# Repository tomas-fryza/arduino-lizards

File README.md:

# Measuring track for lizards

* [TODO](#TODO)
* [About](#About)
* [Usage](#Usage)
  * [PuTTY for Windows and Linux](#PuTTY-for-Windows-and-Linux)
  * [Terminal for Windows](#Terminal-for-Windows)
  * [Termite for Windows](#Termite-for-Windows)
* [Programming Arduino using PlatformIO](#Programming-Arduino-using-PlatformIO)
* [References](#References)

## TODO

* [x] Instructions for use & program
* [x] Logging data to a file
* [x] Selecting a suitable Monitor program (PuTTY, Terminal, Terminte, PlatformIO, ...)
* [x] Strengthen the mechanics
* [x] Add "start box"
* [x] Add (semi)waterproof paint
* [x] Cover electronics, 3D printing
* [x] Q: Consumption? A: approx. 350 milliamps
* [x] Q: IR wavelength A: 940 nm
* [ ] Q: Do I need to install USB driver? A: ??

## About

The measuring path contains 11 optical wounds, i.e. pairs of 940 nm infrared diodes and phototransistors. The first gate is the starting gate, the others are spaced 10 centimeters apart. The length of the track is thus 1 meter. Combine temperature and humidity sensor is used as well.

The ATmega328P microcontroller on the Arduino Nano board provides data acquisition from optical gates, time, temperature and humidity measurement, and data sending. The measuring track is powered via a mini USB connector, and at the same time, all data about the measurement progress is sent to the computer/laptop via this USB. Values are separated by semicolumn ";" symbol and can be subsequently processed, for example, in Excel.

## Usage

Once the microcontroller is programmed, on the PC/laptop just run one of the programs that can communicate with the serial port, such as PuTTY, Terminal, Termite, or other.

Perform the following steps to measure the speed of lizards:

1. Connect your computer/laptop to the Arduino board using a USB cable.

2. Run PuTTY, Terminal, Termite, or other serial terminal.

3. Configure terminal to save measured data to log text file.

4. Press `S` on keyboard to start the measurement. Status LED on Arduino board is turn on.

5. Place the lizard in the starting position and let it run through the entire track.

6. The individual times are written to the serial terminal (and the log file) after all gates have been interrupted or after the maximum time has expired. This is set to 60 seconds and can be reprogrammed in the Arduino Nano.

7. Go back to point 4 and repeat.

### PuTTY for Windows and Linux

1. Download, install, and run PuTTY open-source application for [Windows](https://putty.org/) or [Linux](https://www.tecmint.com/install-putty-on-linux/).

2. Set the following parameters:

   a. Category: Session Logging: **Printable output**

   b. Select Log file name, such as: `C:\Documents\your-user-name\putty_&Y&M&D-&T.log`

   c. Change Category to **Session** and select Connection type: **Serial**

   d. Serial line: put your com port, such as **COM5** (Windows) or `/dev/ttyUSB0` (Linux)

      > **Help:** To get the port name, run the Device Manager on Windows or type `dmesg` command to Terminal in Linux.

   e. Speed: **9600**

   f. Name Save Sessions: **LIZARDS** and click on **Save** button

   g. Anytime in the future, there is no need to configure PuTTY again, just double click on saved default settings **LIZARDS** to open the connection.

   h. Press `S` on keyboard to start each measurement.

   i. Values are saved to your log file.

### Terminal for Windows

1. Download, unzip, and run the [Terminal](https://sites.google.com/site/terminalbpp/) application.

2. TBD

### Termite for Windows

1. Download, install, and run [Termite](https://www.compuphase.com/software_termite.htm#EDITHISTORY) application.

2. TBD

## Programming Arduino using PlatformIO

1. Follow [Installation](https://github.com/tomas-fryza/digital-electronics-2/wiki/How-to-use-AVR-template-with-PlatformIO) instruction and download & install Visual Studio Code and PlatformIO plugin.

2. Download this repository, ie. in [browser](https://github.com/tomas-fryza/arduino-lizards), click on green `<> Code` button and select `Download ZIP`. Extract zip file to your local computer.

3. In Visual Studio Code, select **File > Open Folder...** and browse to `arduino-lizards/software/lizards` extracted folder.

4. In `platformio.ini` configuration file change your port name, such as COM5 for Windows:

   ```asm
   ; Custom monitor port
   ; Windows:
   monitor_port = COM[5]
   ; Linux:
   ; monitor_port = /dev/ttyUSB0
   ```

5. The application is programmed in C++ and is located in the file `src > main.cpp`

6. Compile the code, run the application, and open Serial Monitor to control it.

## References

1. Michaela Ryšavá. [Vývoj systému pro měření pohybových schopností malých živočichů](https://www.vut.cz/studenti/zav-prace/detail/141521)

2. Les Pounder. [How To Detect the COM Port for Any Serial Device in Windows](https://www.tomshardware.com/how-to/detect-com-port-windows-serial-port-notifier)

3. Martins D. Okoi. [How to Install PuTTY on Linux](https://www.tecmint.com/install-putty-on-linux/)

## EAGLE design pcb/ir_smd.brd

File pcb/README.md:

# List of components

Symbol | Value | Package | Description
 :--   | :--   | :--     | :--
R1 | 10k | SMD 0805 | Resistor
R2 | 50 | SMD 0805 | Resistor
C | 100n | SMD 0603 | Capacitor
LM393D | | S08 | Dual differential comparator
L-53F3BT | | THT | LED IR, 940nm, 5mm
503PTC2E | | THT | Phototransistor, IR Detector 940nm
DG350-3.50-05P-14-02A | | | Screw terminal
BL 1 34 G | | | Female headers

## Possible future revisions

* switching transistors for IR leds
* smd packages for both IR leds and phototransistors
* more accurate temperature measurement
* lower consumption, battery powered
* ESP32, wi-fi/bluetooth comm?
* onboard logging: eeprom, sd card, ...
* display, button
* multiple IR LEDs on top of each other; the possibility of setting the necessary height of the optical gate

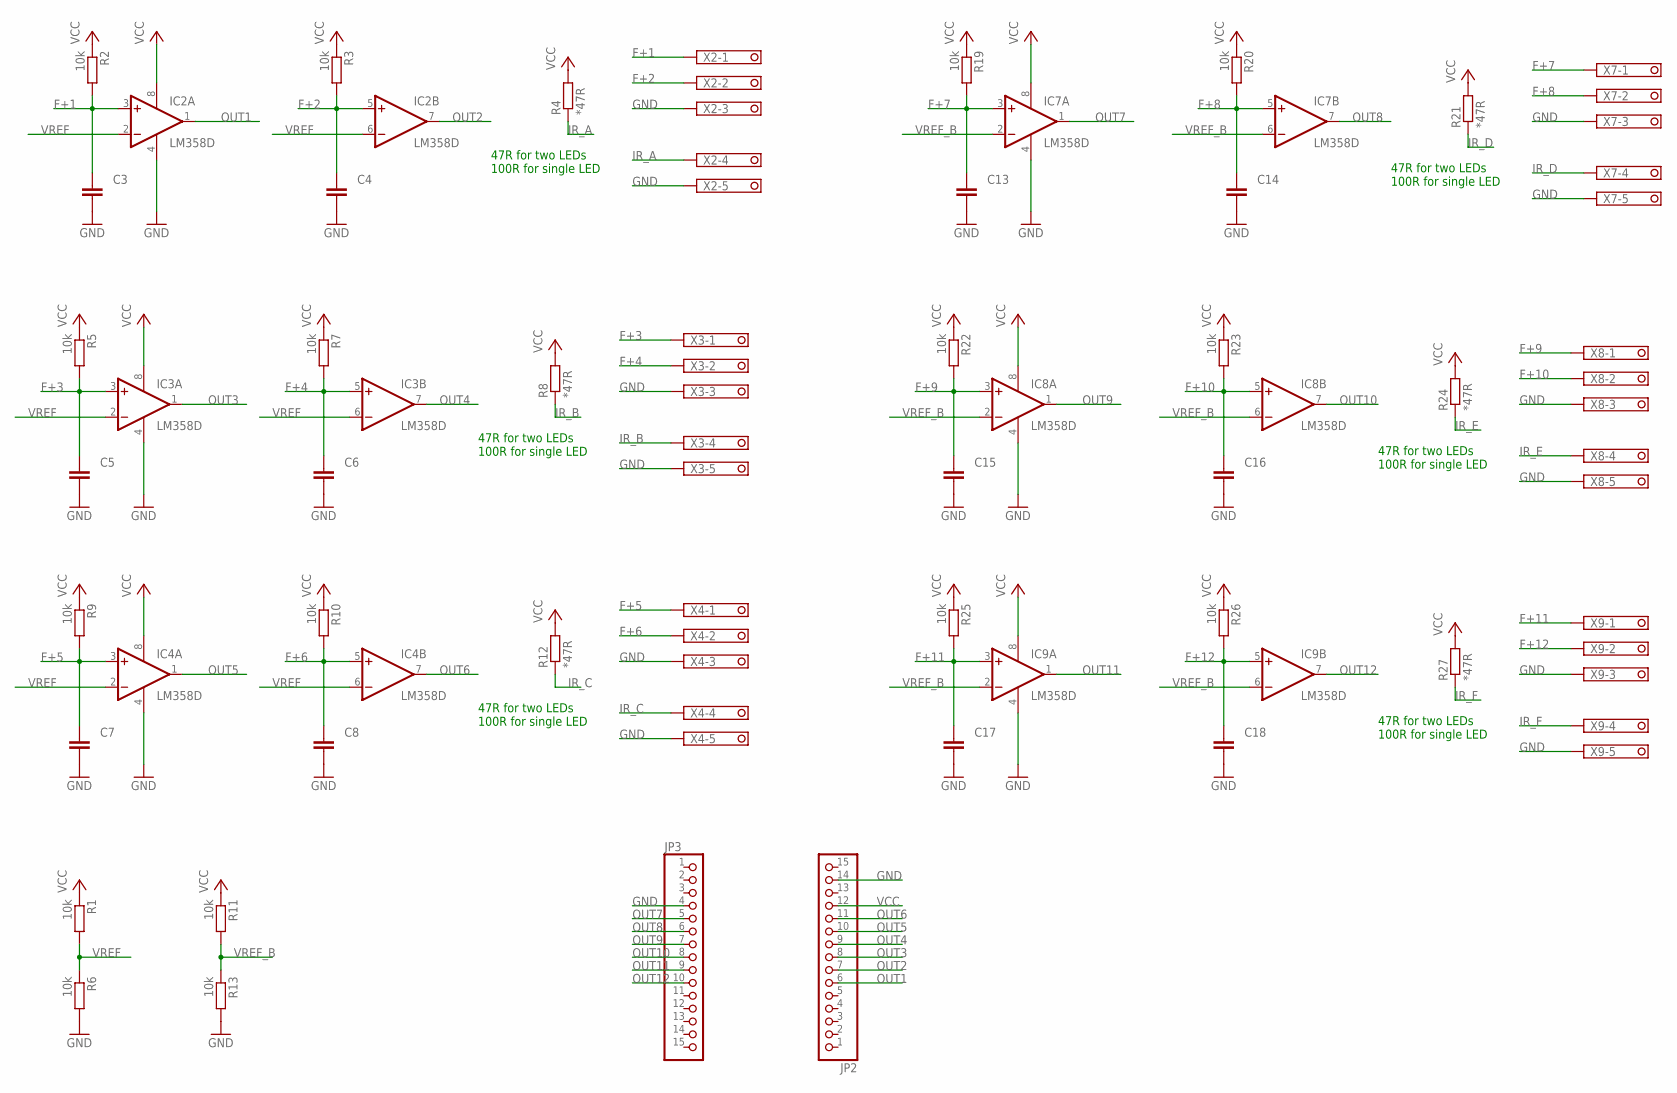
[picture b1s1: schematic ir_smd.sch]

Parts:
C3, C4, C5, C6, C7, C8, C13, C14, C15, C16, C17, C18: C-EUC0603; C0603
IC2, IC3, IC4, IC7, IC8, IC9: LM358D; SO08
JP2, JP3: PINHD-1X15; 1X15
R1, R2, R3, R5, R6, R7, R9, R10, R11, R13, R19, R20, R22, R23, R25, R26: 10k; R0805
R4, R8, R12, R21, R24, R27: *47R; R0805
X2, X3, X4, X7, X8, X9: 1751277

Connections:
F+1: C3.1, IC2.3 (+IN), R2.2, X2.1
F+2: C4.1, IC2.5 (+IN), R3.2, X2.2
F+3: C5.1, IC3.3 (+IN), R5.2, X3.1
F+4: C6.1, IC3.5 (+IN), R7.2, X3.2
F+5: C7.1, IC4.3 (+IN), R9.2, X4.1
F+6: C8.1, IC4.5 (+IN), R10.2, X4.2
F+7: C13.1, IC7.3 (+IN), R19.2, X7.1
F+8: C14.1, IC7.5 (+IN), R20.2, X7.2
F+9: C15.1, IC8.3 (+IN), R22.2, X8.1
F+10: C16.1, IC8.5 (+IN), R23.2, X8.2
F+11: C17.1, IC9.3 (+IN), R25.2, X9.1
F+12: C18.1, IC9.5 (+IN), R26.2, X9.2
GND: C3.2, C4.2, C5.2, C6.2, C7.2, C8.2, C13.2, C14.2, C15.2, C16.2, C17.2, C18.2, IC2.4 (V-), IC3.4 (V-), IC4.4 (V-), IC7.4 (V-), IC8.4 (V-), IC9.4 (V-), JP2.14, JP3.4, R6.2, R13.2, X2.3, X2.5, X3.3, X3.5, X4.3, X4.5, X7.3, X7.5, X8.3, X8.5, X9.3, X9.5
IR_A: R4.1, X2.4
IR_B: R8.1, X3.4
IR_C: R12.1, X4.4
IR_D: R21.1, X7.4
IR_E: R24.1, X8.4
IR_F: R27.1, X9.4
OUT1: IC2.1 (OUT), JP2.6
OUT2: IC2.7 (OUT), JP2.7
OUT3: IC3.1 (OUT), JP2.8
OUT4: IC3.7 (OUT), JP2.9
OUT5: IC4.1 (OUT), JP2.10
OUT6: IC4.7 (OUT), JP2.11
OUT7: IC7.1 (OUT), JP3.5
OUT8: IC7.7 (OUT), JP3.6
OUT9: IC8.1 (OUT), JP3.7
OUT10: IC8.7 (OUT), JP3.8
OUT11: IC9.1 (OUT), JP3.9
OUT12: IC9.7 (OUT), JP3.10
VCC: IC2.8 (V+), IC3.8 (V+), IC4.8 (V+), IC7.8 (V+), IC8.8 (V+), IC9.8 (V+), JP2.12, R1.1, R2.1, R3.1, R4.2, R5.1, R7.1, R8.2, R9.1, R10.1, R11.1, R12.2, R19.1, R20.1, R21.2, R22.1, R23.1, R24.2, R25.1, R26.1, R27.2
VREF: IC2.2 (-IN), IC2.6 (-IN), IC3.2 (-IN), IC3.6 (-IN), IC4.2 (-IN), IC4.6 (-IN), R1.2, R6.1
VREF_B: IC7.2 (-IN), IC7.6 (-IN), IC8.2 (-IN), IC8.6 (-IN), IC9.2 (-IN), IC9.6 (-IN), R11.2, R13.1

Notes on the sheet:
47R for two LEDs 100R for single LED

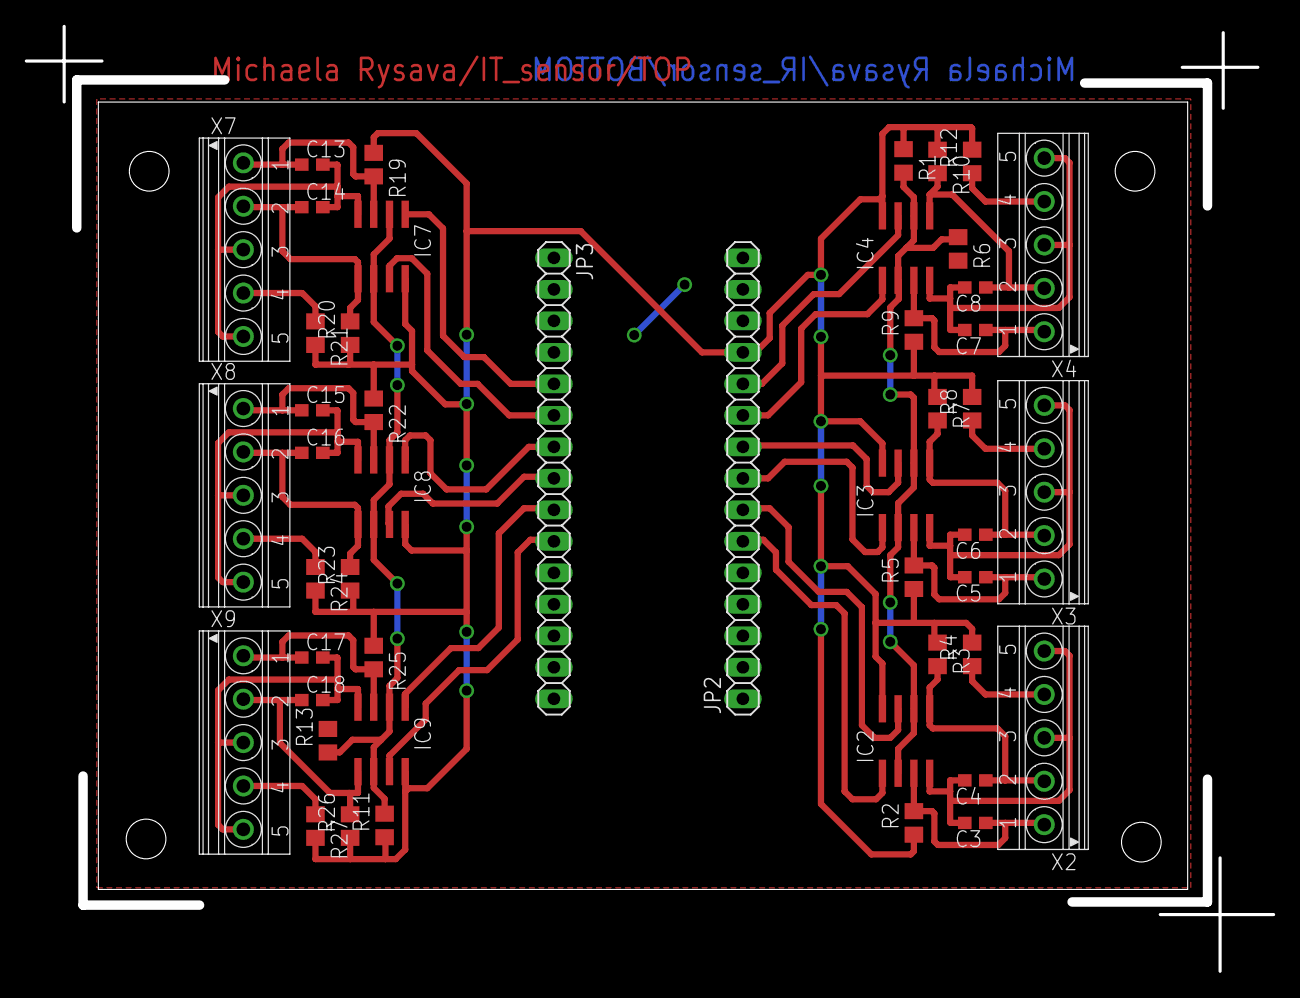
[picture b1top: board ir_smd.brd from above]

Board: 2 copper layers, 100.1 x 75.7 mm, 48 parts (0 on the bottom side), 34 nets.

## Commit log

2023-03-13 Initial commit - Rysava BP
2023-03-13 PlatformIO project created
2023-03-13 Arduino Nano schamatic added
2023-03-13 test input pins
2023-03-14 Monitor speed and port added
2023-03-14 Minor debug prints moved
2023-03-15 Optical gates pin ID corrected
2023-03-16 DHT11 temp and humid senzor added
2023-03-18 Log2file filter added
2023-03-18 Optical gates measurements done and tested
2023-03-18 global variables
2023-03-20 Fist Gekon test
2023-03-20 folders reorganized
2023-03-21 TODO list created
2023-03-21 List of components created
2023-03-21 Links to Win serial monitors added
2023-03-21 Minor comments
2023-03-22 Update README.md
    Several modifs suggested
2023-03-28 Terminal screenshots added
2023-03-28 Serial port Linux
2023-03-29 General info about device and usage created
2023-03-30 PuTTY description finished
2023-03-30 PuTTY decsription finished
2023-04-11 PlatformIO footer image added
2023-04-11 Update README.md
    ToC created
2023-04-12 3D box created, ver1
2023-04-25 Box with cover created
2023-04-26 Measurement ID is shown after "S"
2023-04-30 Add columns to log file
    Prepares empty columns with standard column names for animal ID and body temperature
2023-05-01 Missing semicolumn
2023-05-17 New exit condition
    Stop measurement after the last gate is triggered. Do not wait for all gates to get triggered.
2023-07-14 Update exit condition
    Edit copied from discussion to ensure end of measurement when the last gate is crossed
